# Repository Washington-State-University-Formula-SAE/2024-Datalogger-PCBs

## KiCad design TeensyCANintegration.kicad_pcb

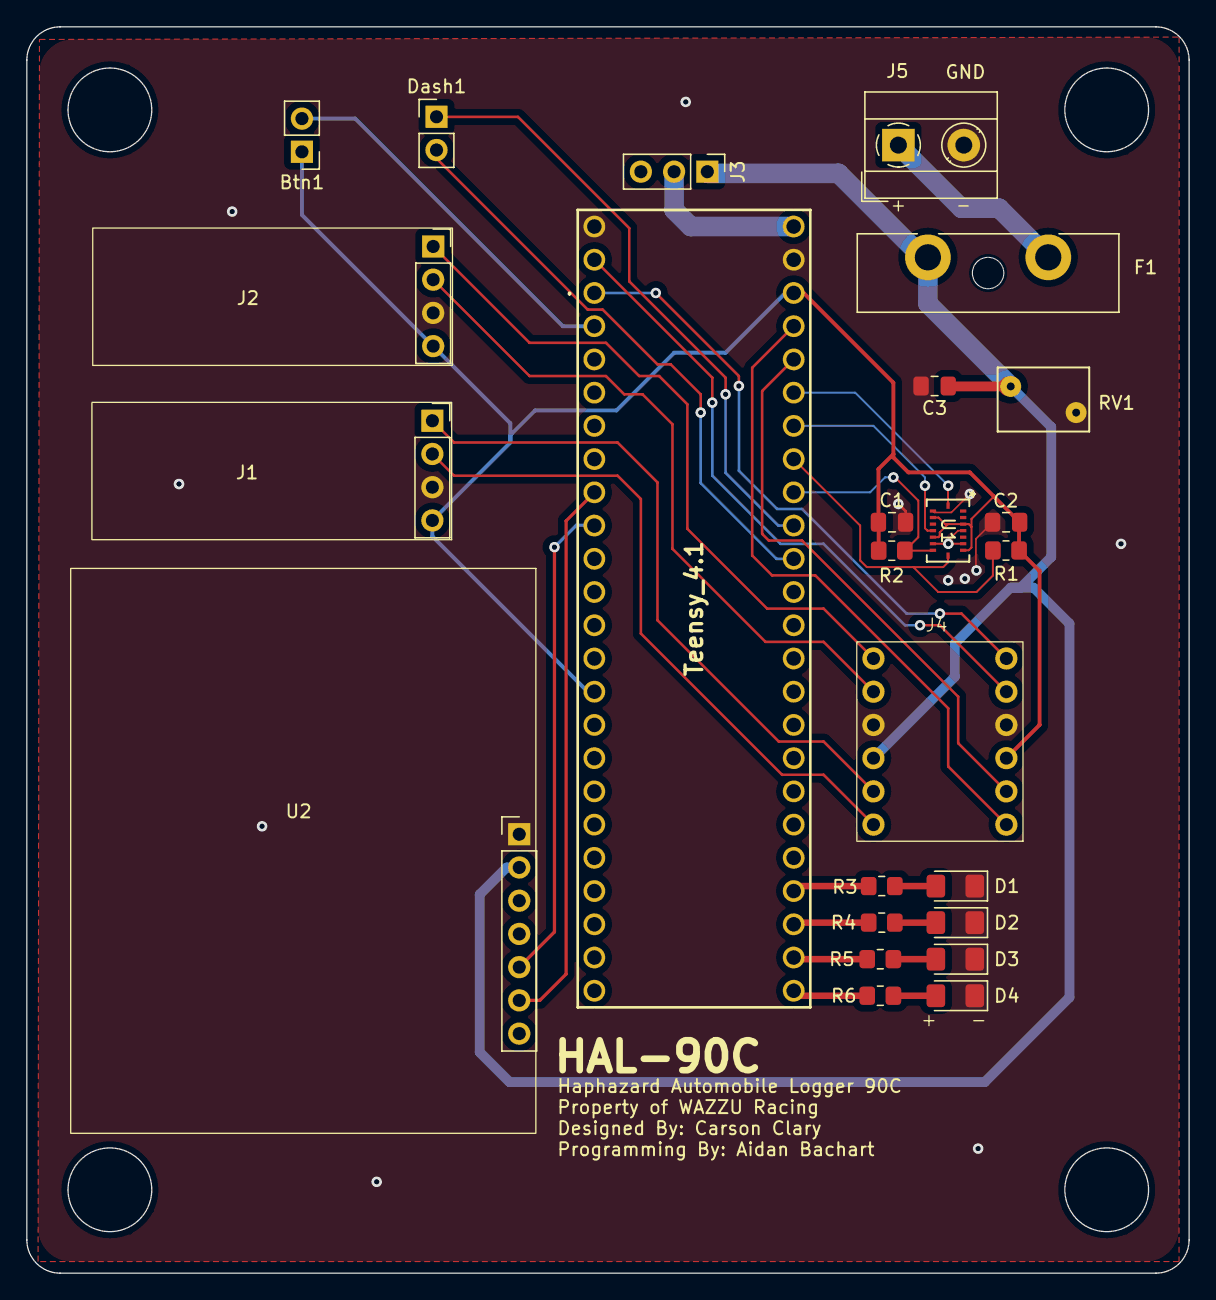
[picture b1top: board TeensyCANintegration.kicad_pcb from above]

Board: 2 copper layers, 88.8 x 95.3 mm, 25 parts (0 on the bottom side), 30 nets.

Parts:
Btn1: Conn_01x02_Pin; PinHeader_1x02_P2.54mm_Vertical
C1, C2: 100nF; C_0805_2012Metric_Pad1.18x1.45mm_HandSolder
C3: 100uF; C_0805_2012Metric_Pad1.18x1.45mm_HandSolder
D1, D2, D3, D4: LED; LED_1206_3216Metric_Pad1.42x1.75mm_HandSolder
Dash1: Conn_01x02_Pin; PinHeader_1x02_P2.54mm_Vertical
F1: 1.5A; Fuseholder_Blade_ATO_Littelfuse_Pudenz_2_Pin
J1: CAN BOB; PinSocket_1x04_P2.54mm_Vertical
J2: CAN BOB; canBOB
J3: Block Jumper; PinHeader_1x03_P2.54mm_Vertical
J4: BOB-12009 Logic Level Shifter; SparkFun Logic Level
J5: Conn_01x02_Pin; TerminalBlock_MetzConnect_Type055_RT01502HDWU_1x02_P5.00mm_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
R1, R2: 2k; R_0805_2012Metric_Pad1.20x1.40mm_HandSolder
R3, R4, R5, R6: 5; R_0805_2012Metric_Pad1.20x1.40mm_HandSolder
RV1: Varistor_US; RV_Disc_D7mm_W4.9mm_P5mm
Teensy_4.1: TEENSY41
U1: BMI088; QFN_BMI085_BOS
U2: NEO-M9N; PinHeader_1x07_P2.54mm_Vertical

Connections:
+3.3V: Btn1.1, C1.1, C2.1, J1.4, J2.4, J4.3, R1.2, R2.1, Teensy_4.1.42 (3.3V), Teensy_4.1.53 (3.3V), U1.3 (VDD), U1.7 (PS), U1.11 (VDDIO), U1.14 (CSB1)
+5V: C3.1, F1.1, J3.1, J4.10, RV1.1, U2.23 (VCC)
/CAN1 RX 3.3v: J4.1, Teensy_4.1.23
/CAN1 RX 5v: J1.2, J4.12
/CAN1 TX 3.3v: J4.2, Teensy_4.1.22
/CAN1 TX 5v: J1.1, J4.11
/CAN2 RX 3.3v: J4.5, Teensy_4.1.0
/CAN2 RX 5v: J2.2, J4.8
/CAN2 TX 3.3v: J4.6, Teensy_4.1.1
/CAN2 TX 5v: J2.1, J4.7
/Dashboard SCL: Dash1.2, Teensy_4.1.16
/Dashboard SDA: Dash1.1, Teensy_4.1.17
/GPS RX: Teensy_4.1.8, U2.21 (RXD/SPI_MOSI)
/GPS TX: Teensy_4.1.7, U2.20 (TXD/SPI_MISO)
/GYRO SCL: R1.1, Teensy_4.1.19, U1.8 (SCL/SCK)
/GYRO SDA: R2.2, Teensy_4.1.18, U1.9 (SDA/SDI)
/IntAccel: Teensy_4.1.21, U1.16 (INT1)
/IntGyro: Teensy_4.1.20, U1.12 (INT3)
/LED0: R3.2, Teensy_4.1.36
/LED1: R4.2, Teensy_4.1.35
/LED2: R5.2, Teensy_4.1.34
/LED3: R6.2, Teensy_4.1.33
/Teensy Vin: J3.2, Teensy_4.1.55 (5V)
/Toggle: Btn1.2, Teensy_4.1.2
GND: C1.2, C2.2, C3.2, D1.1 (K), D2.1 (K), D3.1 (K), D4.1 (K), J1.3, J2.3, J4.4, J4.9, J5.2, RV1.2, Teensy_4.1.70 (Gnd), Teensy_4.1.71 (Gnd), U1.4 (GNDA), U1.6 (GNDIO), U1.10 (SDO2), U1.15 (SDO1), U2.10 (GND)
unnamed: D1.2 (A), R3.1
unnamed: D2.2 (A), R4.1
unnamed: D3.2 (A), R5.1
unnamed: D4.2 (A), R6.1
unnamed: F1.2, J5.1

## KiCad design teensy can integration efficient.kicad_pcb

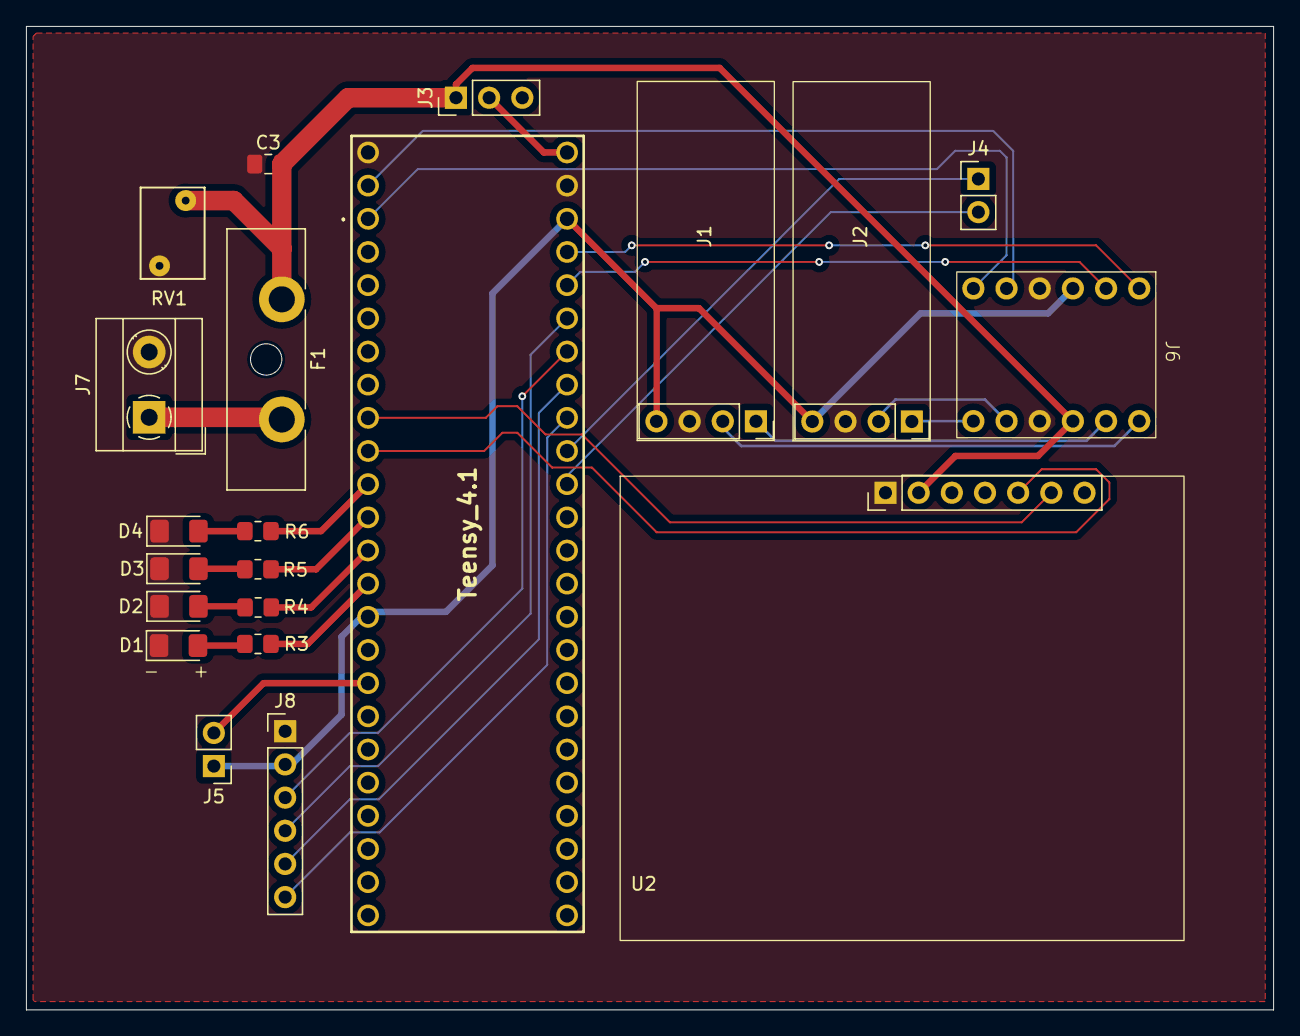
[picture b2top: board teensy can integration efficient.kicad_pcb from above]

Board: 2 copper layers, 95.5 x 75.3 mm, 21 parts (0 on the bottom side), 30 nets.

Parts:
C3: 100uF; C_0805_2012Metric_Pad1.18x1.45mm_HandSolder
D1, D2, D3, D4: LED; LED_1206_3216Metric_Pad1.42x1.75mm_HandSolder
F1: 1.5A; Fuseholder_Blade_ATO_Littelfuse_Pudenz_2_Pin
J1, J2: CAN BOB; canBOB
J3: Block Jumper; PinHeader_1x03_P2.54mm_Vertical
J4, J5: Conn_01x02_Pin; PinHeader_1x02_P2.54mm_Vertical
J6: BOB-12009 Logic Level Shifter; SparkFun Logic Level
J7: Conn_01x02_Pin; TerminalBlock_MetzConnect_Type055_RT01502HDWU_1x02_P5.00mm_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
J8: Conn_01x06_Pin; PinHeader_1x06_P2.54mm_Vertical
R3, R4, R5, R6: 5; R_0805_2012Metric_Pad1.20x1.40mm_HandSolder
RV1: Varistor_US; RV_Disc_D7mm_W4.9mm_P5mm
Teensy_4.1: TEENSY41
U2: NEO-M9N; NEO-M9N GPS

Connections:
+3.3V: J1.4, J2.4, J5.1, J6.3, J8.2, Teensy_4.1.42 (3.3V), Teensy_4.1.53 (3.3V)
+5V: C3.1, F1.1, J3.1, J6.10, RV1.1, U2.23 (VCC)
/CAN1 RX 3.3v: J6.1, Teensy_4.1.23
/CAN1 RX 5v: J1.2, J6.12
/CAN1 TX 3.3v: J6.2, Teensy_4.1.22
/CAN1 TX 5v: J1.1, J6.11
/CAN2 RX 3.3v: J6.5, Teensy_4.1.0
/CAN2 RX 5v: J2.2, J6.8
/CAN2 TX 3.3v: J6.6, Teensy_4.1.1
/CAN2 TX 5v: J2.1, J6.7
/Dashboard SCL: J4.2, Teensy_4.1.16
/Dashboard SDA: J4.1, Teensy_4.1.17
/GPS RX: Teensy_4.1.8, U2.21 (RXD/SPI_MOSI)
/GPS TX: Teensy_4.1.7, U2.20 (TXD/SPI_MISO)
/GYRO SCL: J8.5, Teensy_4.1.19
/GYRO SDA: J8.6, Teensy_4.1.18
/IntAccel: J8.4, Teensy_4.1.21
/IntGyro: J8.3, Teensy_4.1.20
/LED0: R3.2, Teensy_4.1.12
/LED1: R4.2, Teensy_4.1.11
/LED2: R5.2, Teensy_4.1.10
/LED3: R6.2, Teensy_4.1.9
/Teensy Vin: J3.2, Teensy_4.1.55 (5V)
/Toggle: J5.2, Teensy_4.1.25
GND: C3.2, D1.1 (K), D2.1 (K), D3.1 (K), D4.1 (K), J1.3, J2.3, J6.4, J6.9, J7.2, J8.1, RV1.2, Teensy_4.1.70 (Gnd), Teensy_4.1.71 (Gnd), U2.10 (GND)
unnamed: D1.2 (A), R3.1
unnamed: D2.2 (A), R4.1
unnamed: D3.2 (A), R5.1
unnamed: D4.2 (A), R6.1
unnamed: F1.2, J7.1

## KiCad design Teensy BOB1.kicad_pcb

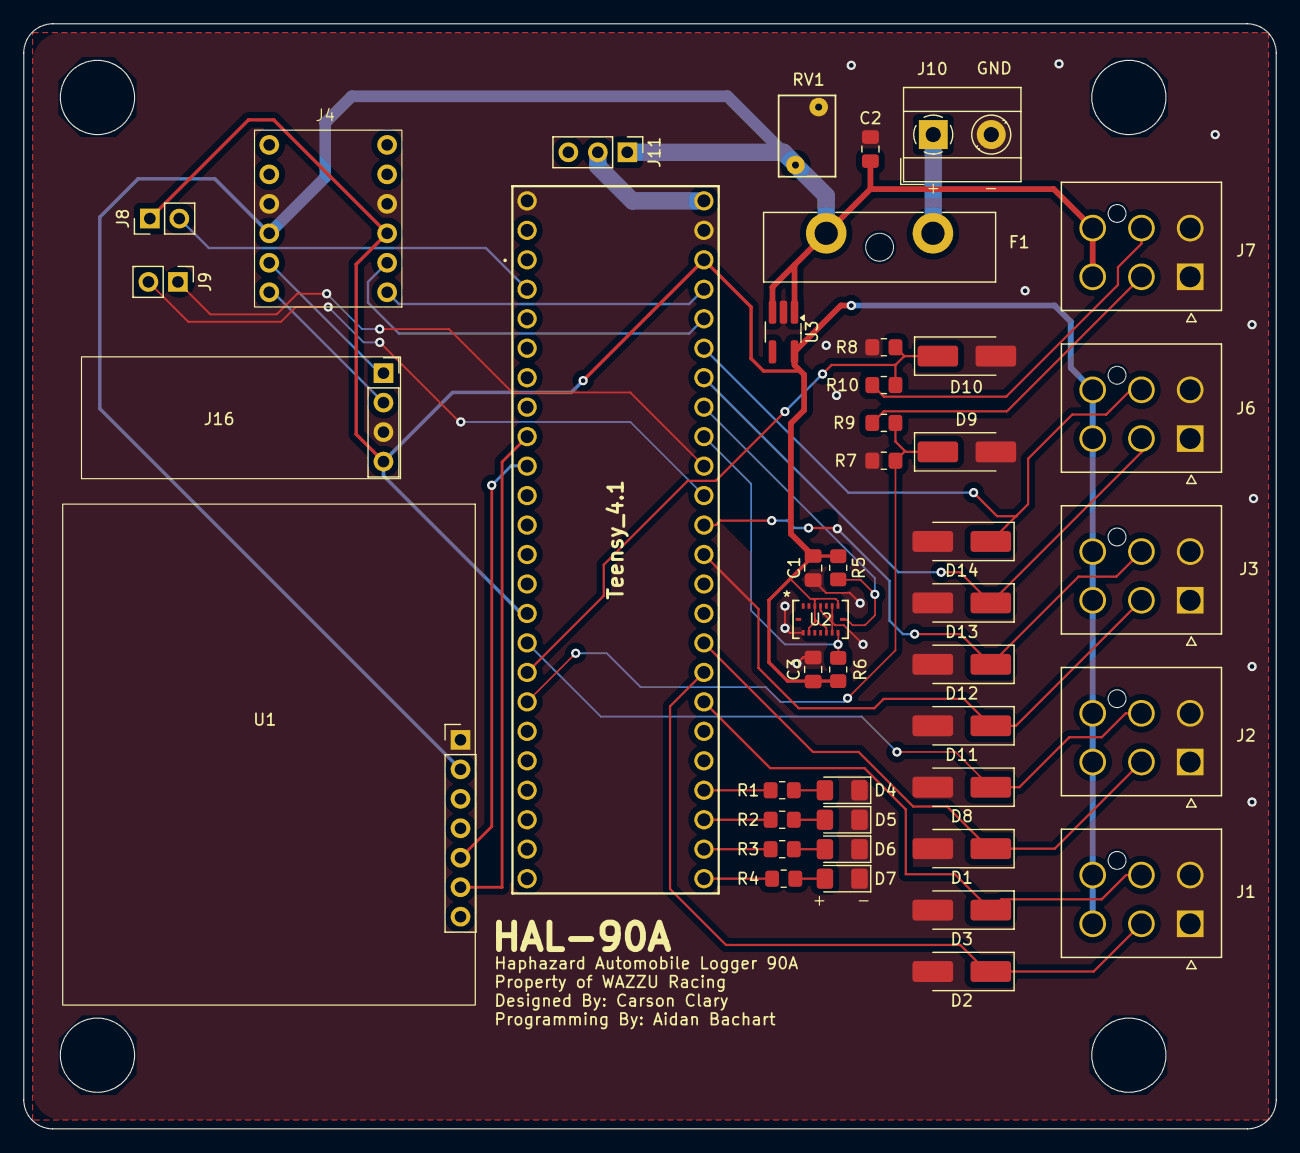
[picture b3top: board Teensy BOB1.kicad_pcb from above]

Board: 2 copper layers, 107.9 x 95.2 mm, 44 parts (0 on the bottom side), 36 nets.

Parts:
C1, C3: 100nF; C_0805_2012Metric_Pad1.18x1.45mm_HandSolder
C2: 100uF; C_0805_2012Metric_Pad1.18x1.45mm_HandSolder
D1, D2, D3, D8, D9, D10, D11, D12, D13, D14: D_Zener; D_SMA_Handsoldering
D4, D5, D6, D7: LED; LED_1206_3216Metric_Pad1.42x1.75mm_HandSolder
F1: 1.5A; Fuseholder_Blade_ATO_Littelfuse_Pudenz_2_Pin
J1, J2, J3, J6, J7: Conn_02x03_Counter_Clockwise; MOLEX_2125201006
J4: BOB-12009 Logic Level Shifter; SparkFun Logic Level
J8, J9: Conn_01x02_Pin; PinHeader_1x02_P2.54mm_Vertical
J10: Conn_01x02_Pin; TerminalBlock_MetzConnect_Type055_RT01502HDWU_1x02_P5.00mm_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
J11: Block Jumper; PinHeader_1x03_P2.54mm_Vertical
J16: CAN BOB; PinSocket_1x04_P2.54mm_Vertical
R1, R2, R3, R4: 5; R_0805_2012Metric_Pad1.20x1.40mm_HandSolder
R5, R6, R7, R8: 2k; R_0805_2012Metric_Pad1.20x1.40mm_HandSolder
R9, R10: 1.1k; R_0805_2012Metric_Pad1.20x1.40mm_HandSolder
RV1: Varistor_US; RV_Disc_D7mm_W4.9mm_P5mm
Teensy_4.1: TEENSY41
U1: NEO-M9N; PinHeader_1x07_P2.54mm_Vertical
U2: BMI088; QFN_BMI085_BOS
U3: TLV73310PDBVT; TSOT-23-5_HandSoldering

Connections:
+3.3V: C1.1, C3.1, J1.3, J1.6, J2.3, J2.6, J3.3, J3.6, J4.3, J6.3, J6.6, J8.1, J16.4, R5.2, R6.1, Teensy_4.1.42 (3.3V), Teensy_4.1.53 (3.3V), U2.3 (VDD), U2.7 (PS), U2.11 (VDDIO), U2.14 (CSB1), U3.5 (OUT)
+5V: C2.1, F1.1, J4.10, J7.3, J7.6, J11.1, RV1.1, U1.23 (VCC), U3.1 (IN), U3.3 (EN)
/Amb Temp: D1.1 (K), J2.2, Teensy_4.1.41
/CAN1 RX 3.3v: J4.1, Teensy_4.1.23
/CAN1 RX 5v: J4.12, J16.2
/CAN1 TX 3.3v: J4.2, Teensy_4.1.22
/CAN1 TX 5v: J4.11, J16.1
/Dashboard SCL: J9.2, Teensy_4.1.16
/Dashboard SDA: J9.1, Teensy_4.1.17
/GPS RX: Teensy_4.1.8, U1.21 (RXD/SPI_MOSI)
/GPS TX: Teensy_4.1.7, U1.20 (TXD/SPI_MISO)
/GYRO SCL: R5.1, Teensy_4.1.19, U2.8 (SCL/SCK)
/GYRO SDA: R6.2, Teensy_4.1.18, U2.9 (SDA/SDI)
/LB_Pressure: D9.1 (K), R7.1, R9.2, Teensy_4.1.26
/LED0: R1.2, Teensy_4.1.36
/LED1: R2.2, Teensy_4.1.35
/LED2: R3.2, Teensy_4.1.34
/LED3: R4.2, Teensy_4.1.33
/RB_Pressure: D10.1 (K), R8.1, R10.2, Teensy_4.1.25
/RadIn Temp: D2.1 (K), J1.2, Teensy_4.1.40
/RadOut Temp: D3.1 (K), J1.5, Teensy_4.1.39
/Steering: D8.1 (K), J2.5, Teensy_4.1.24
/Suspension0: D11.1 (K), J3.2, Teensy_4.1.14
/Suspension1: D12.1 (K), J3.5, Teensy_4.1.15
/Suspension2: D13.1 (K), J6.2, Teensy_4.1.20
/Suspension3: D14.1 (K), J6.5, Teensy_4.1.21
/Teensy Vin: J11.2, Teensy_4.1.55 (5V)
/Toggle: J8.2, Teensy_4.1.2
GND: C1.2, C2.2, C3.2, D1.2 (A), D2.2 (A), D3.2 (A), D4.1 (K), D5.1 (K), D6.1 (K), D7.1 (K), D8.2 (A), D9.2 (A), D10.2 (A), D11.2 (A), D12.2 (A), D13.2 (A), D14.2 (A), J1.1, J1.4, J2.1, J2.4, J3.1, J3.4, J4.4, J4.9, J6.1, J6.4, J7.1, J7.4, J10.2, J16.3, R7.2, R8.2, RV1.2, Teensy_4.1.70 (Gnd), Teensy_4.1.71 (Gnd), U1.10 (GND), U2.4 (GNDA), U2.6 (GNDIO), U2.10 (SDO2), U2.15 (SDO1), U3.2 (GND)
unnamed: D4.2 (A), R1.1
unnamed: D5.2 (A), R2.1
unnamed: D6.2 (A), R3.1
unnamed: D7.2 (A), R4.1
unnamed: J7.2, R9.1
unnamed: J7.5, R10.1
unnamed: F1.2, J10.1

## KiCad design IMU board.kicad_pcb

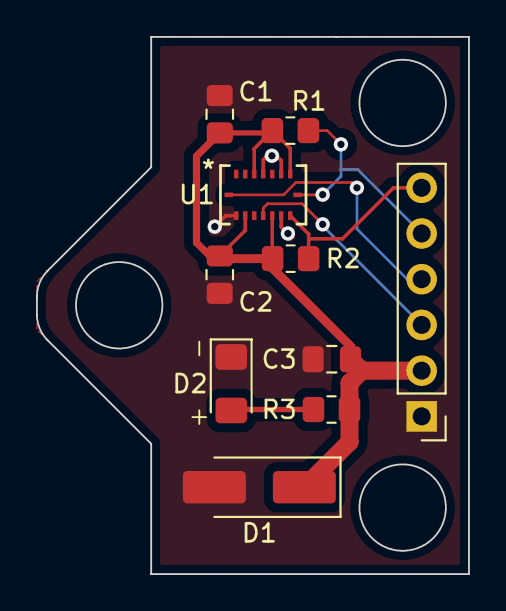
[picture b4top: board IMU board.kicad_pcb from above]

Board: 2 copper layers, 24.0 x 29.8 mm, 10 parts (0 on the bottom side), 7 nets.

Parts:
C1, C2: 100nF; C_0805_2012Metric_Pad1.18x1.45mm_HandSolder
C3: 100uF; C_0805_2012Metric_Pad1.18x1.45mm_HandSolder
D1: D_Zener; D_SMA_Handsoldering
D2: LED; LED_1206_3216Metric_Pad1.42x1.75mm_HandSolder
J2: Conn_01x06_Pin; PinHeader_1x06_P2.54mm_Vertical
R1, R2: 2k; R_0805_2012Metric_Pad1.20x1.40mm_HandSolder
R3: 5; R_0805_2012Metric_Pad1.20x1.40mm_HandSolder
U1: BMI088; QFN_BMI085_BOS

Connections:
+3.3V: C1.1, C2.1, C3.1, D1.1 (K), J2.2, R1.2, R2.1, R3.2, U1.3 (VDD), U1.7 (PS), U1.11 (VDDIO), U1.14 (CSB1)
/GYRO SCL: J2.5, R1.1, U1.8 (SCL/SCK)
/GYRO SDA: J2.6, R2.2, U1.9 (SDA/SDI)
/IntAccel: J2.4, U1.16 (INT1)
/IntGyro: J2.3, U1.12 (INT3)
GND: C1.2, C2.2, C3.2, D1.2 (A), D2.1 (K), J2.1, U1.4 (GNDA), U1.6 (GNDIO), U1.10 (SDO2), U1.15 (SDO1)
unnamed: D2.2 (A), R3.1
